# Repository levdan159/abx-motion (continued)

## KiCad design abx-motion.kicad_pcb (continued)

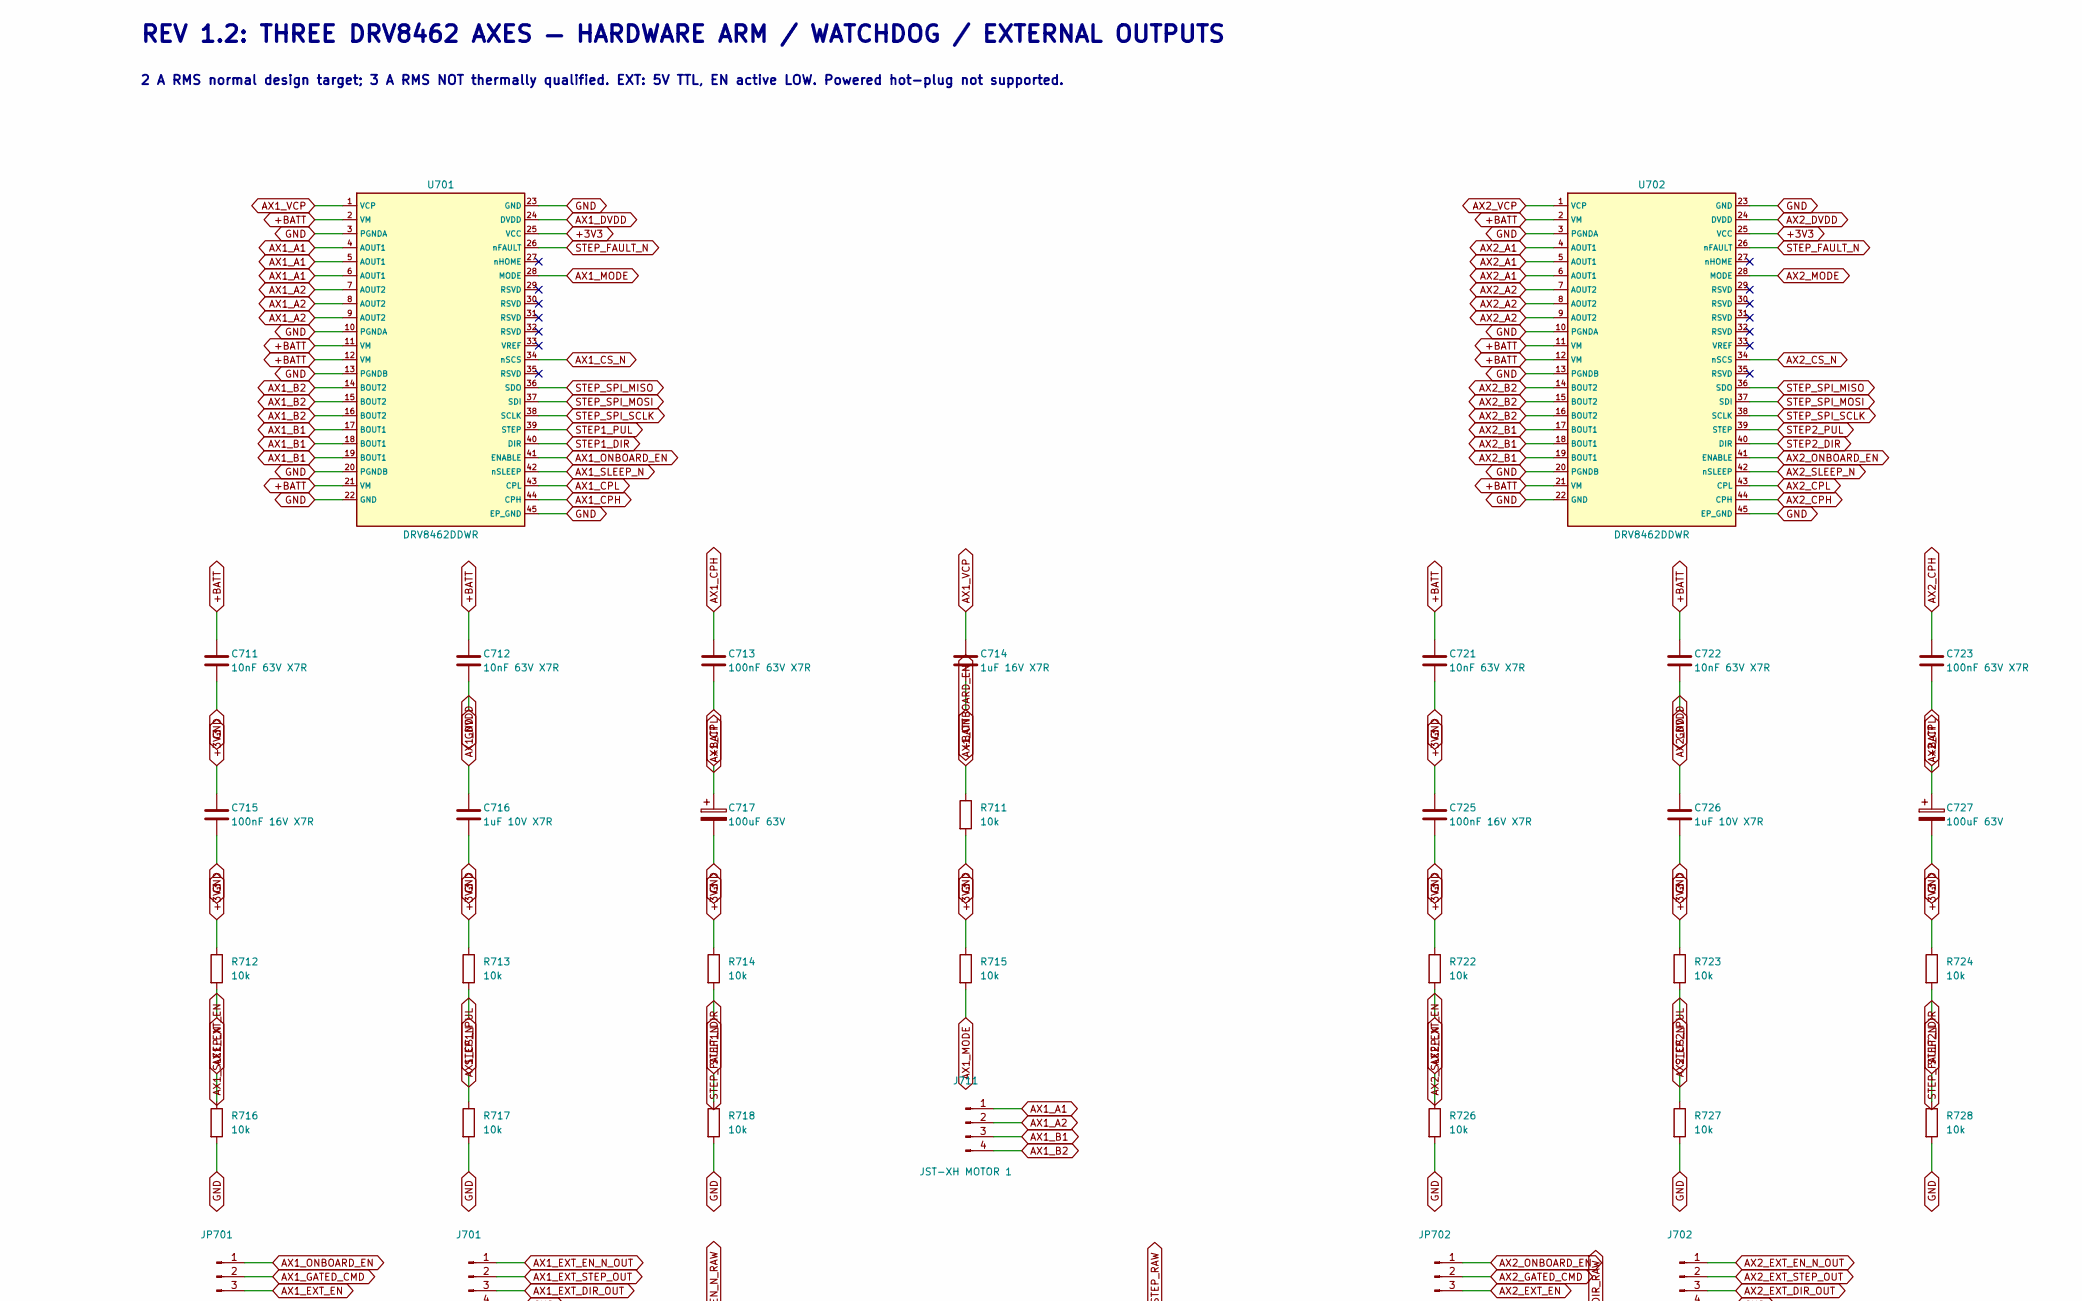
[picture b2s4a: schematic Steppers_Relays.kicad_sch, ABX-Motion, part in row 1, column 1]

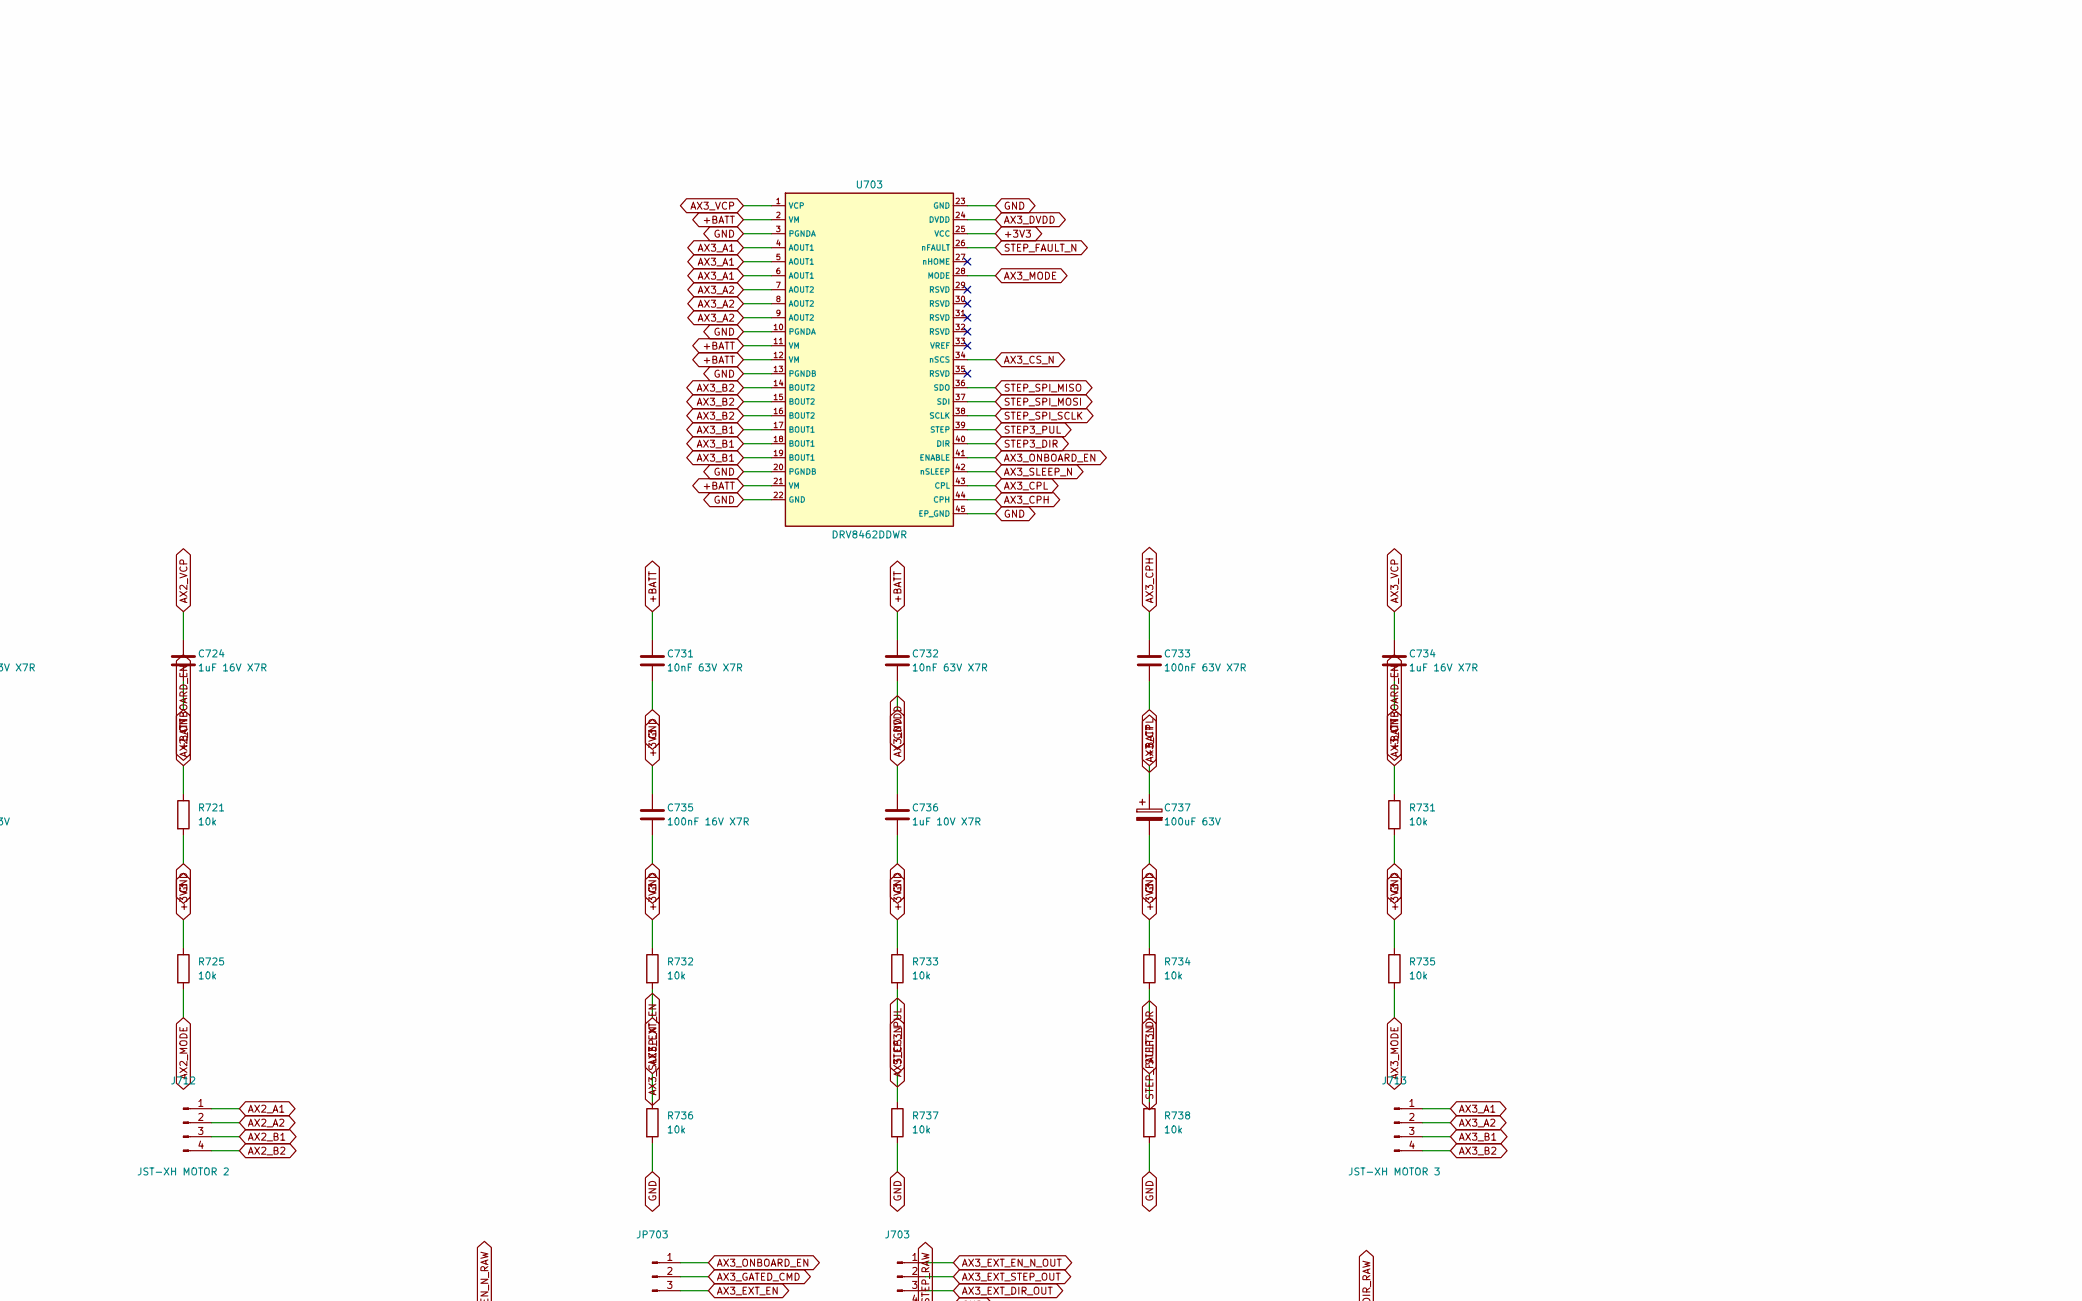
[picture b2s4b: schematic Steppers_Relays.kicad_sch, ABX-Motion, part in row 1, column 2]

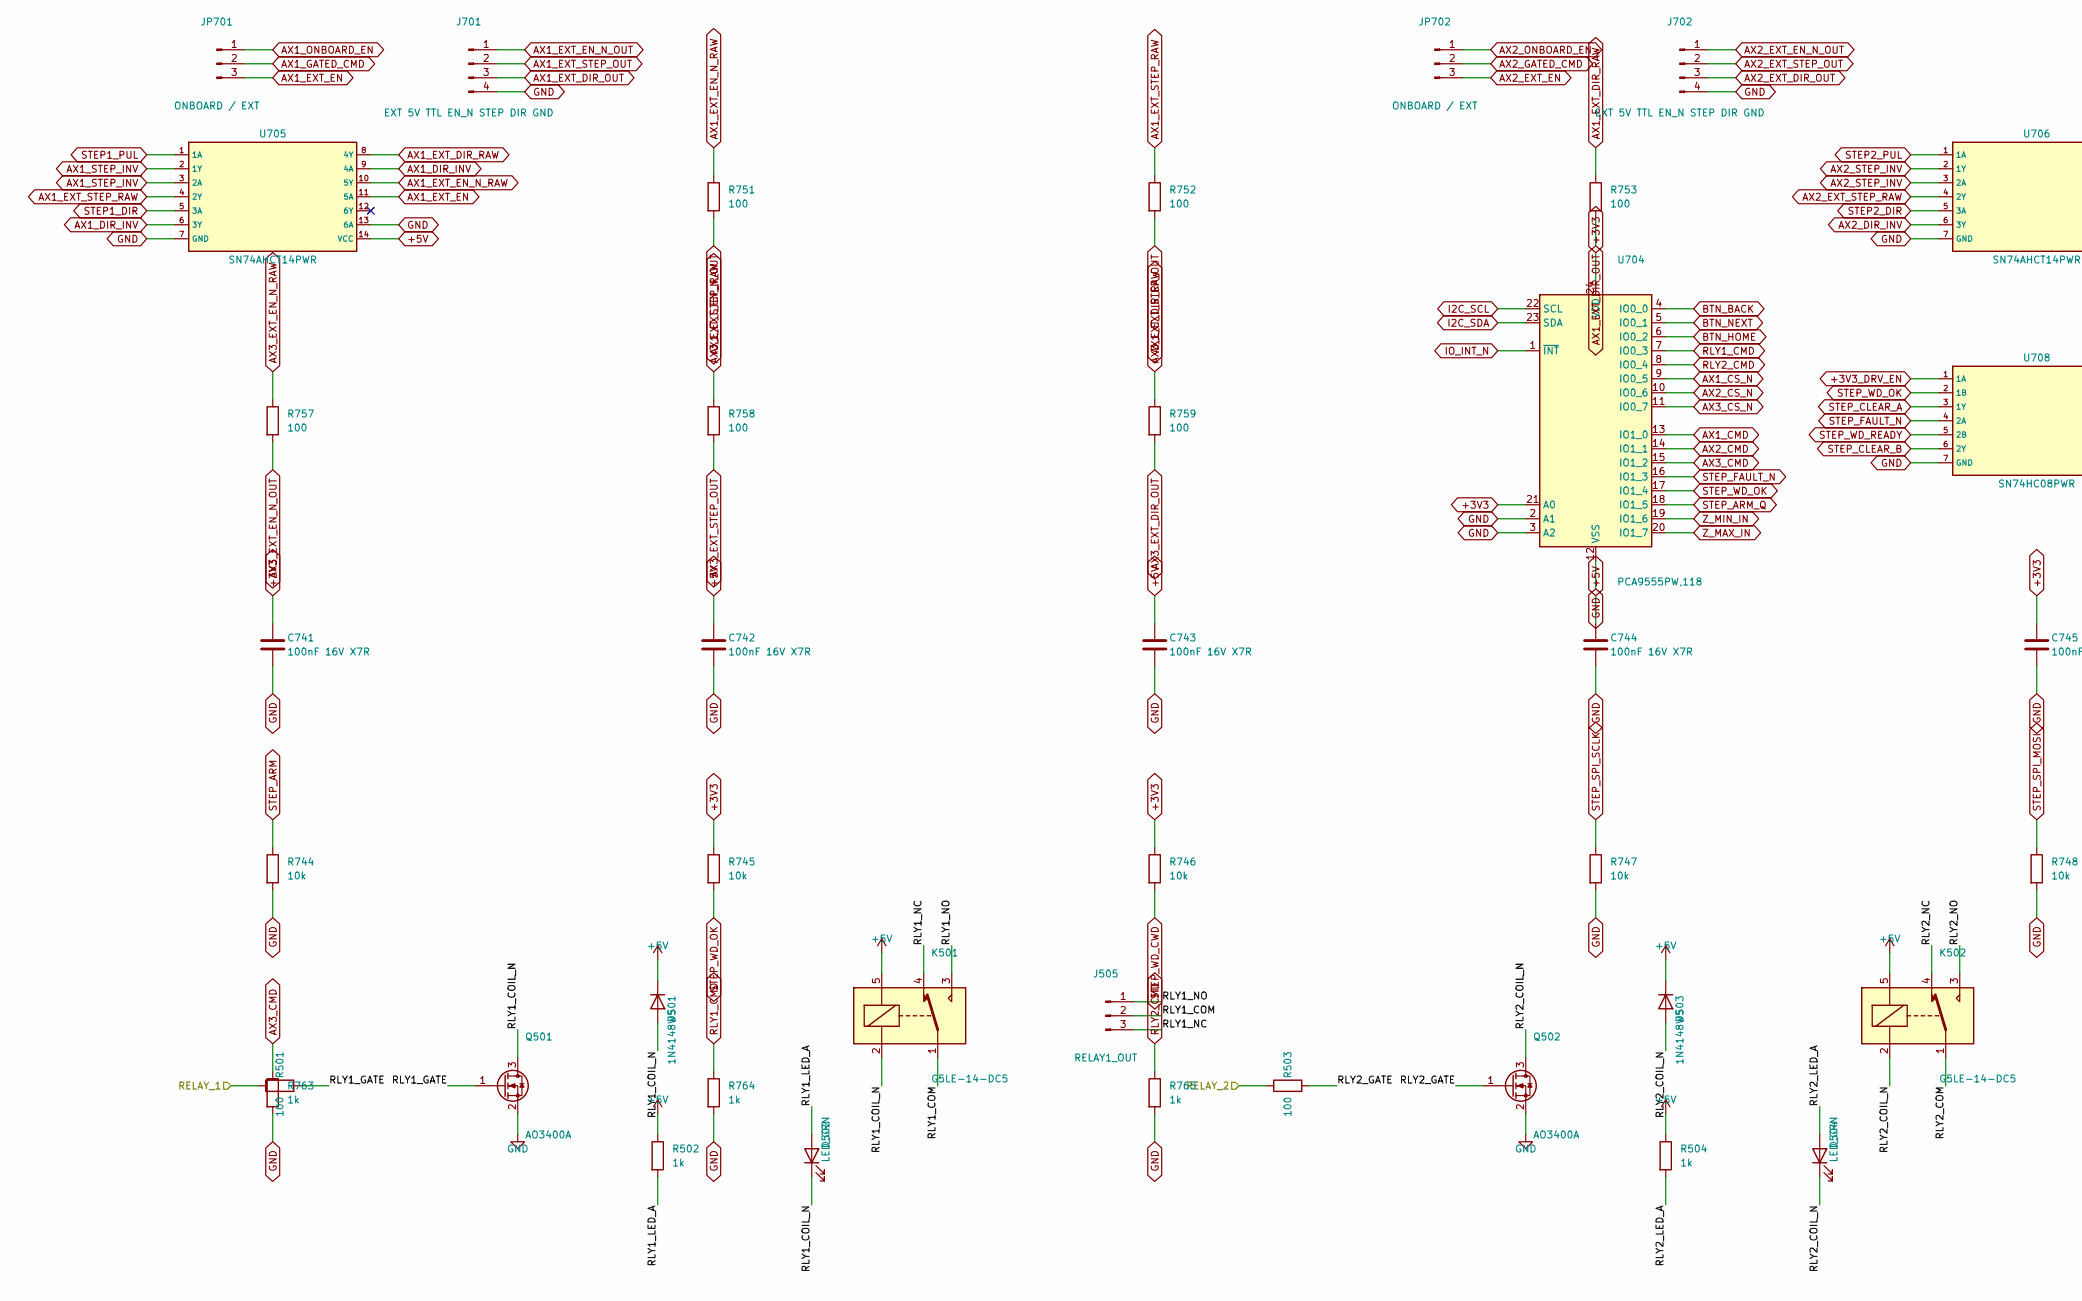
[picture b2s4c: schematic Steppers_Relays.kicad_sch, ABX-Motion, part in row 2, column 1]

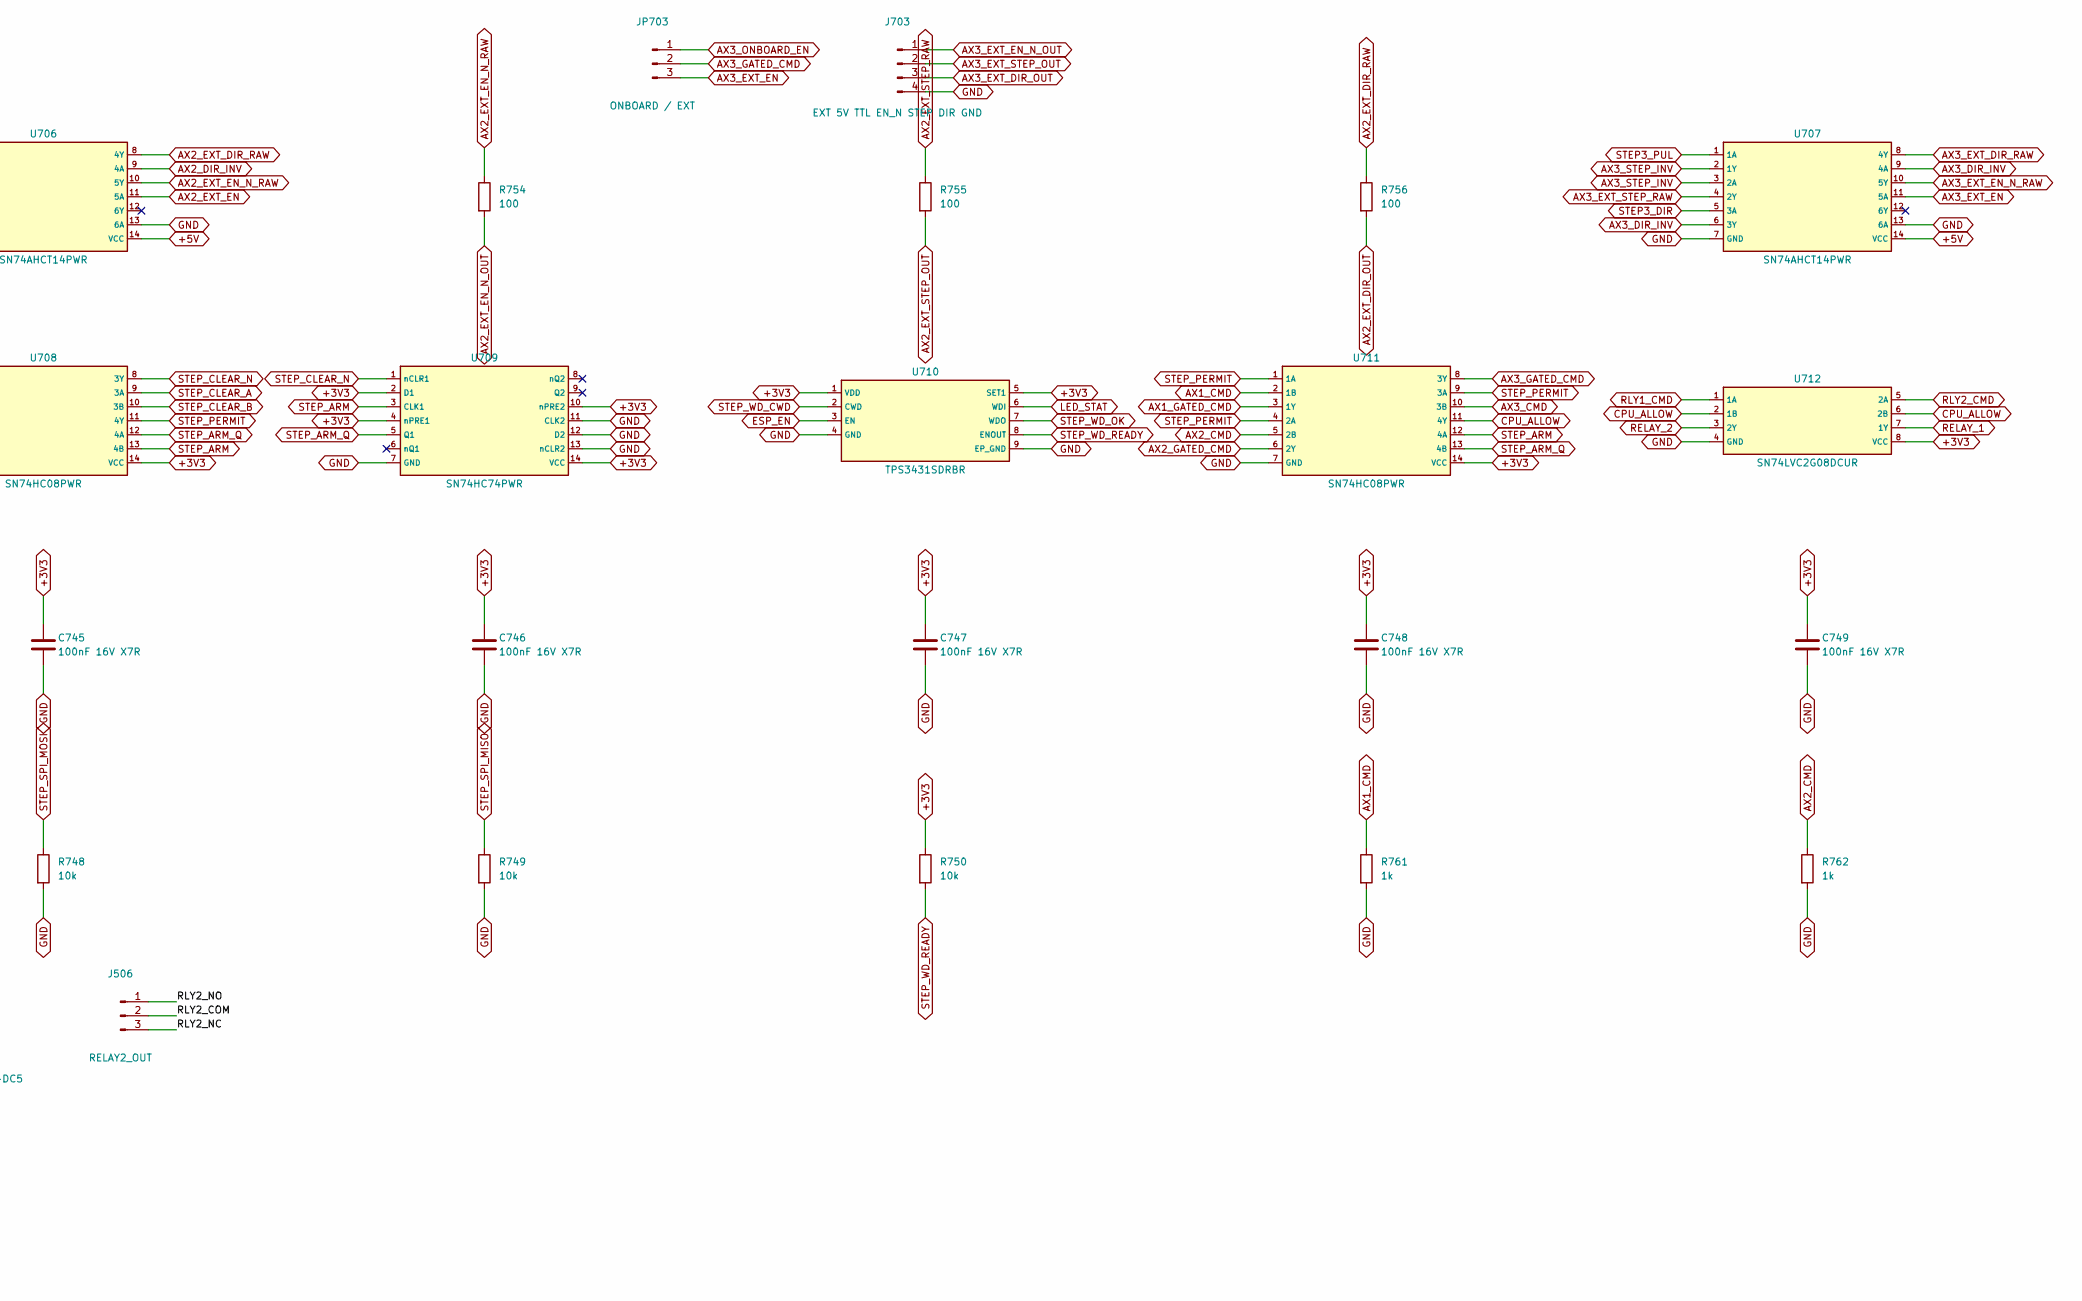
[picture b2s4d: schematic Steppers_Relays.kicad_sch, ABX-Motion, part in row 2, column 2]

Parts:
C711, C712, C721, C722, C731, C732: 10nF 63V X7R; C_0603_1608Metric; LCSC C162275
C713, C723, C733: 100nF 63V X7R; C_0603_1608Metric; LCSC C77058
C714, C724, C734: 1uF 16V X7R; C_0603_1608Metric; LCSC C59782
C715, C725, C735, C741, C742, C743, C744, C745, C746, C747, C748, C749: 100nF 16V X7R; C_0603_1608Metric; LCSC C14663
C716, C726, C736: 1uF 10V X7R; C_0603_1608Metric; LCSC C59782
C717, C727, C737: 100uF 63V; CP_Radial_D8.0mm_P3.50mm; LCSC C88747
D501, D503: 1N4148WS; D_SOD-323; LCSC C2128
D502, D504: LED_GRN; LED_0603_1608Metric; LCSC C12624
J505: RELAY1_OUT; ABX_J505_TerminalBlock_Phoenix_MKDS-1_5-3-5.08_1x03_P5.08mm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; LCSC C72334
J506: RELAY2_OUT; ABX_J506_TerminalBlock_Phoenix_MKDS-1_5-3-5.08_1x03_P5.08mm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; LCSC C72334
J701, J702, J703: EXT 5V TTL EN_N STEP DIR GND; PinHeader_1x04_P2.54mm_Vertical; LCSC C492403
J711: JST-XH MOTOR 1; JST_XH_B4B-XH-A_1x04_P2.50mm_Vertical; LCSC C566014
J712: JST-XH MOTOR 2; JST_XH_B4B-XH-A_1x04_P2.50mm_Vertical; LCSC C566014
J713: JST-XH MOTOR 3; JST_XH_B4B-XH-A_1x04_P2.50mm_Vertical; LCSC C566014
JP701, JP702, JP703: ONBOARD / EXT; PinHeader_1x03_P2.54mm_Vertical; LCSC C492402
K501, K502: G5LE-14-DC5; Relay_SPDT_Omron-G5LE-1; LCSC C116963
Q501, Q502: AO3400A; SOT-23; LCSC C20917
R501, R503, R751, R752, R753, R754, R755, R756, R757, R758, R759: 100; R_0603_1608Metric; LCSC C22775
R502, R504, R761, R762, R763, R764, R765: 1k; R_0603_1608Metric; LCSC C21190
R711, R712, R713, R714, R715, R716, R717, R718, R721, R722, R723, R724, R725, R726, R727, R728, R731, R732, R733, R734, R735, R736, R737, R738, R744, R745, R746, R747, R748, R749, R750: 10k; R_0603_1608Metric; LCSC C25804
U701, U702, U703: DRV8462DDWR; DRV8462_DDW0044E; LCSC C5930226
U704: PCA9555PW,118; TSSOP-24_4.4x7.8mm_P0.65mm; LCSC C128392
U705, U706, U707: SN74AHCT14PWR; TSSOP-14_4.4x5mm_P0.65mm; LCSC C7481
U708, U711: SN74HC08PWR; TSSOP-14_4.4x5mm_P0.65mm; LCSC C7642
U709: SN74HC74PWR; TSSOP-14_4.4x5mm_P0.65mm; LCSC C6761
U710: TPS3431SDRBR; TPS3431_DRB0008A; LCSC C702145
U712: SN74LVC2G08DCUR; VSSOP-8_2.3x2mm_P0.5mm; LCSC C91875

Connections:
+3V3: C715.1, C725.1, C735.1, C741.1, C745.1, C746.1, C747.1, C748.1, C749.1, R712.1, R713.1, R714.1, R715.1, R722.1, R723.1, R724.1, R725.1, R732.1, R733.1, R734.1, R735.1, R745.1, R746.1, R750.1, U701.25 (VCC), U702.25 (VCC), U703.25 (VCC), U704.21 (A0), U704.24 (VDD), U708.14 (VCC), U709.2 (D1), U709.4 (nPRE1), U709.10 (nPRE2), U709.14 (VCC), U710.1 (VDD), U710.5 (SET1), U711.14 (VCC), U712.8 (VCC); also elsewhere on the board
+3V3_DRV_EN: U708.1 (1A); also elsewhere on the board
+5V: C742.1, C743.1, C744.1, D501.1 (K), D503.1 (K), K501.5, K502.5, R502.1, R504.1, U705.14 (VCC), U706.14 (VCC), U707.14 (VCC); also elsewhere on the board
/Steppers_and_Relays/RLY1_COIL_N: D501.2 (A), D502.1 (K), K501.2, Q501.3 (D)
/Steppers_and_Relays/RLY1_COM: J505.2, K501.1
/Steppers_and_Relays/RLY1_GATE: Q501.1 (G), R501.2
/Steppers_and_Relays/RLY1_LED_A: D502.2 (A), R502.2
/Steppers_and_Relays/RLY1_NC: J505.3, K501.4
/Steppers_and_Relays/RLY1_NO: J505.1, K501.3
/Steppers_and_Relays/RLY2_COIL_N: D503.2 (A), D504.1 (K), K502.2, Q502.3 (D)
/Steppers_and_Relays/RLY2_COM: J506.2, K502.1
/Steppers_and_Relays/RLY2_GATE: Q502.1 (G), R503.2
/Steppers_and_Relays/RLY2_LED_A: D504.2 (A), R504.2
/Steppers_and_Relays/RLY2_NC: J506.3, K502.4
/Steppers_and_Relays/RLY2_NO: J506.1, K502.3
AX1_A1: J711.1, U701.4 (AOUT1), U701.5 (AOUT1), U701.6 (AOUT1)
AX1_A2: J711.2, U701.7 (AOUT2), U701.8 (AOUT2), U701.9 (AOUT2)
AX1_B1: J711.3, U701.17 (BOUT1), U701.18 (BOUT1), U701.19 (BOUT1)
AX1_B2: J711.4, U701.14 (BOUT2), U701.15 (BOUT2), U701.16 (BOUT2)
AX1_CMD: R761.1, U704.13 (IO1_0), U711.2 (1B)
AX1_CPH: C713.1, U701.44 (CPH)
AX1_CPL: C713.2, U701.43 (CPL)
AX1_CS_N: R713.2, U701.34 (nSCS), U704.9 (IO0_5)
AX1_DIR_INV: U705.6 (3Y), U705.9 (4A)
AX1_DVDD: C716.1, U701.24 (DVDD)
AX1_EXT_DIR_OUT: J701.3, R753.2
AX1_EXT_DIR_RAW: R753.1, U705.8 (4Y)
AX1_EXT_EN: JP701.3, R716.1, U705.11 (5A)
AX1_EXT_EN_N_OUT: J701.1, R751.2
AX1_EXT_EN_N_RAW: R751.1, U705.10 (5Y)
AX1_EXT_STEP_OUT: J701.2, R752.2
AX1_EXT_STEP_RAW: R752.1, U705.4 (2Y)
AX1_GATED_CMD: JP701.2, U711.3 (1Y)
AX1_MODE: R715.2, U701.28 (MODE)
AX1_ONBOARD_EN: JP701.1, R711.1, U701.41 (ENABLE)
AX1_SLEEP_N: R712.2, U701.42 (nSLEEP)
AX1_STEP_INV: U705.2 (1Y), U705.3 (2A)
AX1_VCP: C714.1, U701.1 (VCP)
AX2_A1: J712.1, U702.4 (AOUT1), U702.5 (AOUT1), U702.6 (AOUT1)
AX2_A2: J712.2, U702.7 (AOUT2), U702.8 (AOUT2), U702.9 (AOUT2)
AX2_B1: J712.3, U702.17 (BOUT1), U702.18 (BOUT1), U702.19 (BOUT1)
AX2_B2: J712.4, U702.14 (BOUT2), U702.15 (BOUT2), U702.16 (BOUT2)
AX2_CMD: R762.1, U704.14 (IO1_1), U711.5 (2B)
AX2_CPH: C723.1, U702.44 (CPH)
AX2_CPL: C723.2, U702.43 (CPL)
AX2_CS_N: R723.2, U702.34 (nSCS), U704.10 (IO0_6)
AX2_DIR_INV: U706.6 (3Y), U706.9 (4A)
AX2_DVDD: C726.1, U702.24 (DVDD)
AX2_EXT_DIR_OUT: J702.3, R756.2
AX2_EXT_DIR_RAW: R756.1, U706.8 (4Y)
AX2_EXT_EN: JP702.3, R726.1, U706.11 (5A)
AX2_EXT_EN_N_OUT: J702.1, R754.2
AX2_EXT_EN_N_RAW: R754.1, U706.10 (5Y)
AX2_EXT_STEP_OUT: J702.2, R755.2
AX2_EXT_STEP_RAW: R755.1, U706.4 (2Y)
AX2_GATED_CMD: JP702.2, U711.6 (2Y)
AX2_MODE: R725.2, U702.28 (MODE)
AX2_ONBOARD_EN: JP702.1, R721.1, U702.41 (ENABLE)
AX2_SLEEP_N: R722.2, U702.42 (nSLEEP)
AX2_STEP_INV: U706.2 (1Y), U706.3 (2A)
AX2_VCP: C724.1, U702.1 (VCP)
AX3_A1: J713.1, U703.4 (AOUT1), U703.5 (AOUT1), U703.6 (AOUT1)
AX3_A2: J713.2, U703.7 (AOUT2), U703.8 (AOUT2), U703.9 (AOUT2)
AX3_B1: J713.3, U703.17 (BOUT1), U703.18 (BOUT1), U703.19 (BOUT1)
AX3_B2: J713.4, U703.14 (BOUT2), U703.15 (BOUT2), U703.16 (BOUT2)
AX3_CMD: R763.1, U704.15 (IO1_2), U711.10 (3B)
AX3_CPH: C733.1, U703.44 (CPH)
AX3_CPL: C733.2, U703.43 (CPL)
AX3_CS_N: R733.2, U703.34 (nSCS), U704.11 (IO0_7)
AX3_DIR_INV: U707.6 (3Y), U707.9 (4A)
AX3_DVDD: C736.1, U703.24 (DVDD)
AX3_EXT_DIR_OUT: J703.3, R759.2
AX3_EXT_DIR_RAW: R759.1, U707.8 (4Y)
AX3_EXT_EN: JP703.3, R736.1, U707.11 (5A)
AX3_EXT_EN_N_OUT: J703.1, R757.2
AX3_EXT_EN_N_RAW: R757.1, U707.10 (5Y)
AX3_EXT_STEP_OUT: J703.2, R758.2
AX3_EXT_STEP_RAW: R758.1, U707.4 (2Y)
AX3_GATED_CMD: JP703.2, U711.8 (3Y)
AX3_MODE: R735.2, U703.28 (MODE)
AX3_ONBOARD_EN: JP703.1, R731.1, U703.41 (ENABLE)
AX3_SLEEP_N: R732.2, U703.42 (nSLEEP)
AX3_STEP_INV: U707.2 (1Y), U707.3 (2A)
AX3_VCP: C734.1, U703.1 (VCP)
BTN_BACK: U704.4 (IO0_0); also elsewhere on the board
BTN_HOME: U704.6 (IO0_2); also elsewhere on the board
BTN_NEXT: U704.5 (IO0_1); also elsewhere on the board
CPU_ALLOW: U711.11 (4Y), U712.2 (1B), U712.6 (2B)
ESP_EN: U710.3 (EN); also elsewhere on the board
I2C_SCL: U704.22 (SCL); also elsewhere on the board
I2C_SDA: U704.23 (SDA); also elsewhere on the board
IO_INT_N: U704.1 (~INT); also elsewhere on the board
LED_STAT: U710.6 (WDI); also elsewhere on the board
RELAY_1: R501.1, U712.7 (1Y); also elsewhere on the board
RELAY_2: R503.1, U712.3 (2Y); also elsewhere on the board
RLY1_CMD: R764.1, U704.7 (IO0_3), U712.1 (1A)
RLY2_CMD: R765.1, U704.8 (IO0_4), U712.5 (2A)
STEP1_DIR: R718.1, U701.40 (DIR), U705.5 (3A); also elsewhere on the board
STEP1_PUL: R717.1, U701.39 (STEP), U705.1 (1A); also elsewhere on the board
STEP2_DIR: R728.1, U702.40 (DIR), U706.5 (3A); also elsewhere on the board
STEP2_PUL: R727.1, U702.39 (STEP), U706.1 (1A); also elsewhere on the board
STEP3_DIR: R738.1, U703.40 (DIR), U707.5 (3A); also elsewhere on the board
STEP3_PUL: R737.1, U703.39 (STEP), U707.1 (1A); also elsewhere on the board
STEP_ARM: R744.1, U708.13 (4B), U709.3 (CLK1), U711.12 (4A); also elsewhere on the board
STEP_ARM_Q: U704.18 (IO1_5), U708.12 (4A), U709.5 (Q1), U711.13 (4B)
STEP_CLEAR_A: U708.3 (1Y), U708.9 (3A)
STEP_CLEAR_B: U708.6 (2Y), U708.10 (3B)
STEP_CLEAR_N: U708.8 (3Y), U709.1 (nCLR1)
STEP_FAULT_N: R714.2, R724.2, R734.2, U701.26 (nFAULT), U702.26 (nFAULT), U703.26 (nFAULT), U704.16 (IO1_3), U708.4 (2A)
STEP_PERMIT: U708.11 (4Y), U711.1 (1A), U711.4 (2A), U711.9 (3A)
STEP_SPI_MISO: R749.1, U701.36 (SDO), U702.36 (SDO), U703.36 (SDO); also elsewhere on the board
STEP_SPI_MOSI: R748.1, U701.37 (SDI), U702.37 (SDI), U703.37 (SDI); also elsewhere on the board
STEP_SPI_SCLK: R747.1, U701.38 (SCLK), U702.38 (SCLK), U703.38 (SCLK); also elsewhere on the board
STEP_WD_CWD: R746.2, U710.2 (CWD)
STEP_WD_OK: R745.2, U704.17 (IO1_4), U708.2 (1B), U710.7 (WDO)
STEP_WD_READY: R750.2, U708.5 (2B), U710.8 (ENOUT)
Z_MAX_IN: U704.20 (IO1_7); also elsewhere on the board
Z_MIN_IN: U704.19 (IO1_6); also elsewhere on the board

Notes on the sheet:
REV 1.2: THREE DRV8462 AXES — HARDWARE ARM / WATCHDOG / EXTERNAL OUTPUTS
2 A RMS normal design target; 3 A RMS NOT thermally qualified. EXT: 5V TTL, EN active LOW. Powered hot-plug not supported.

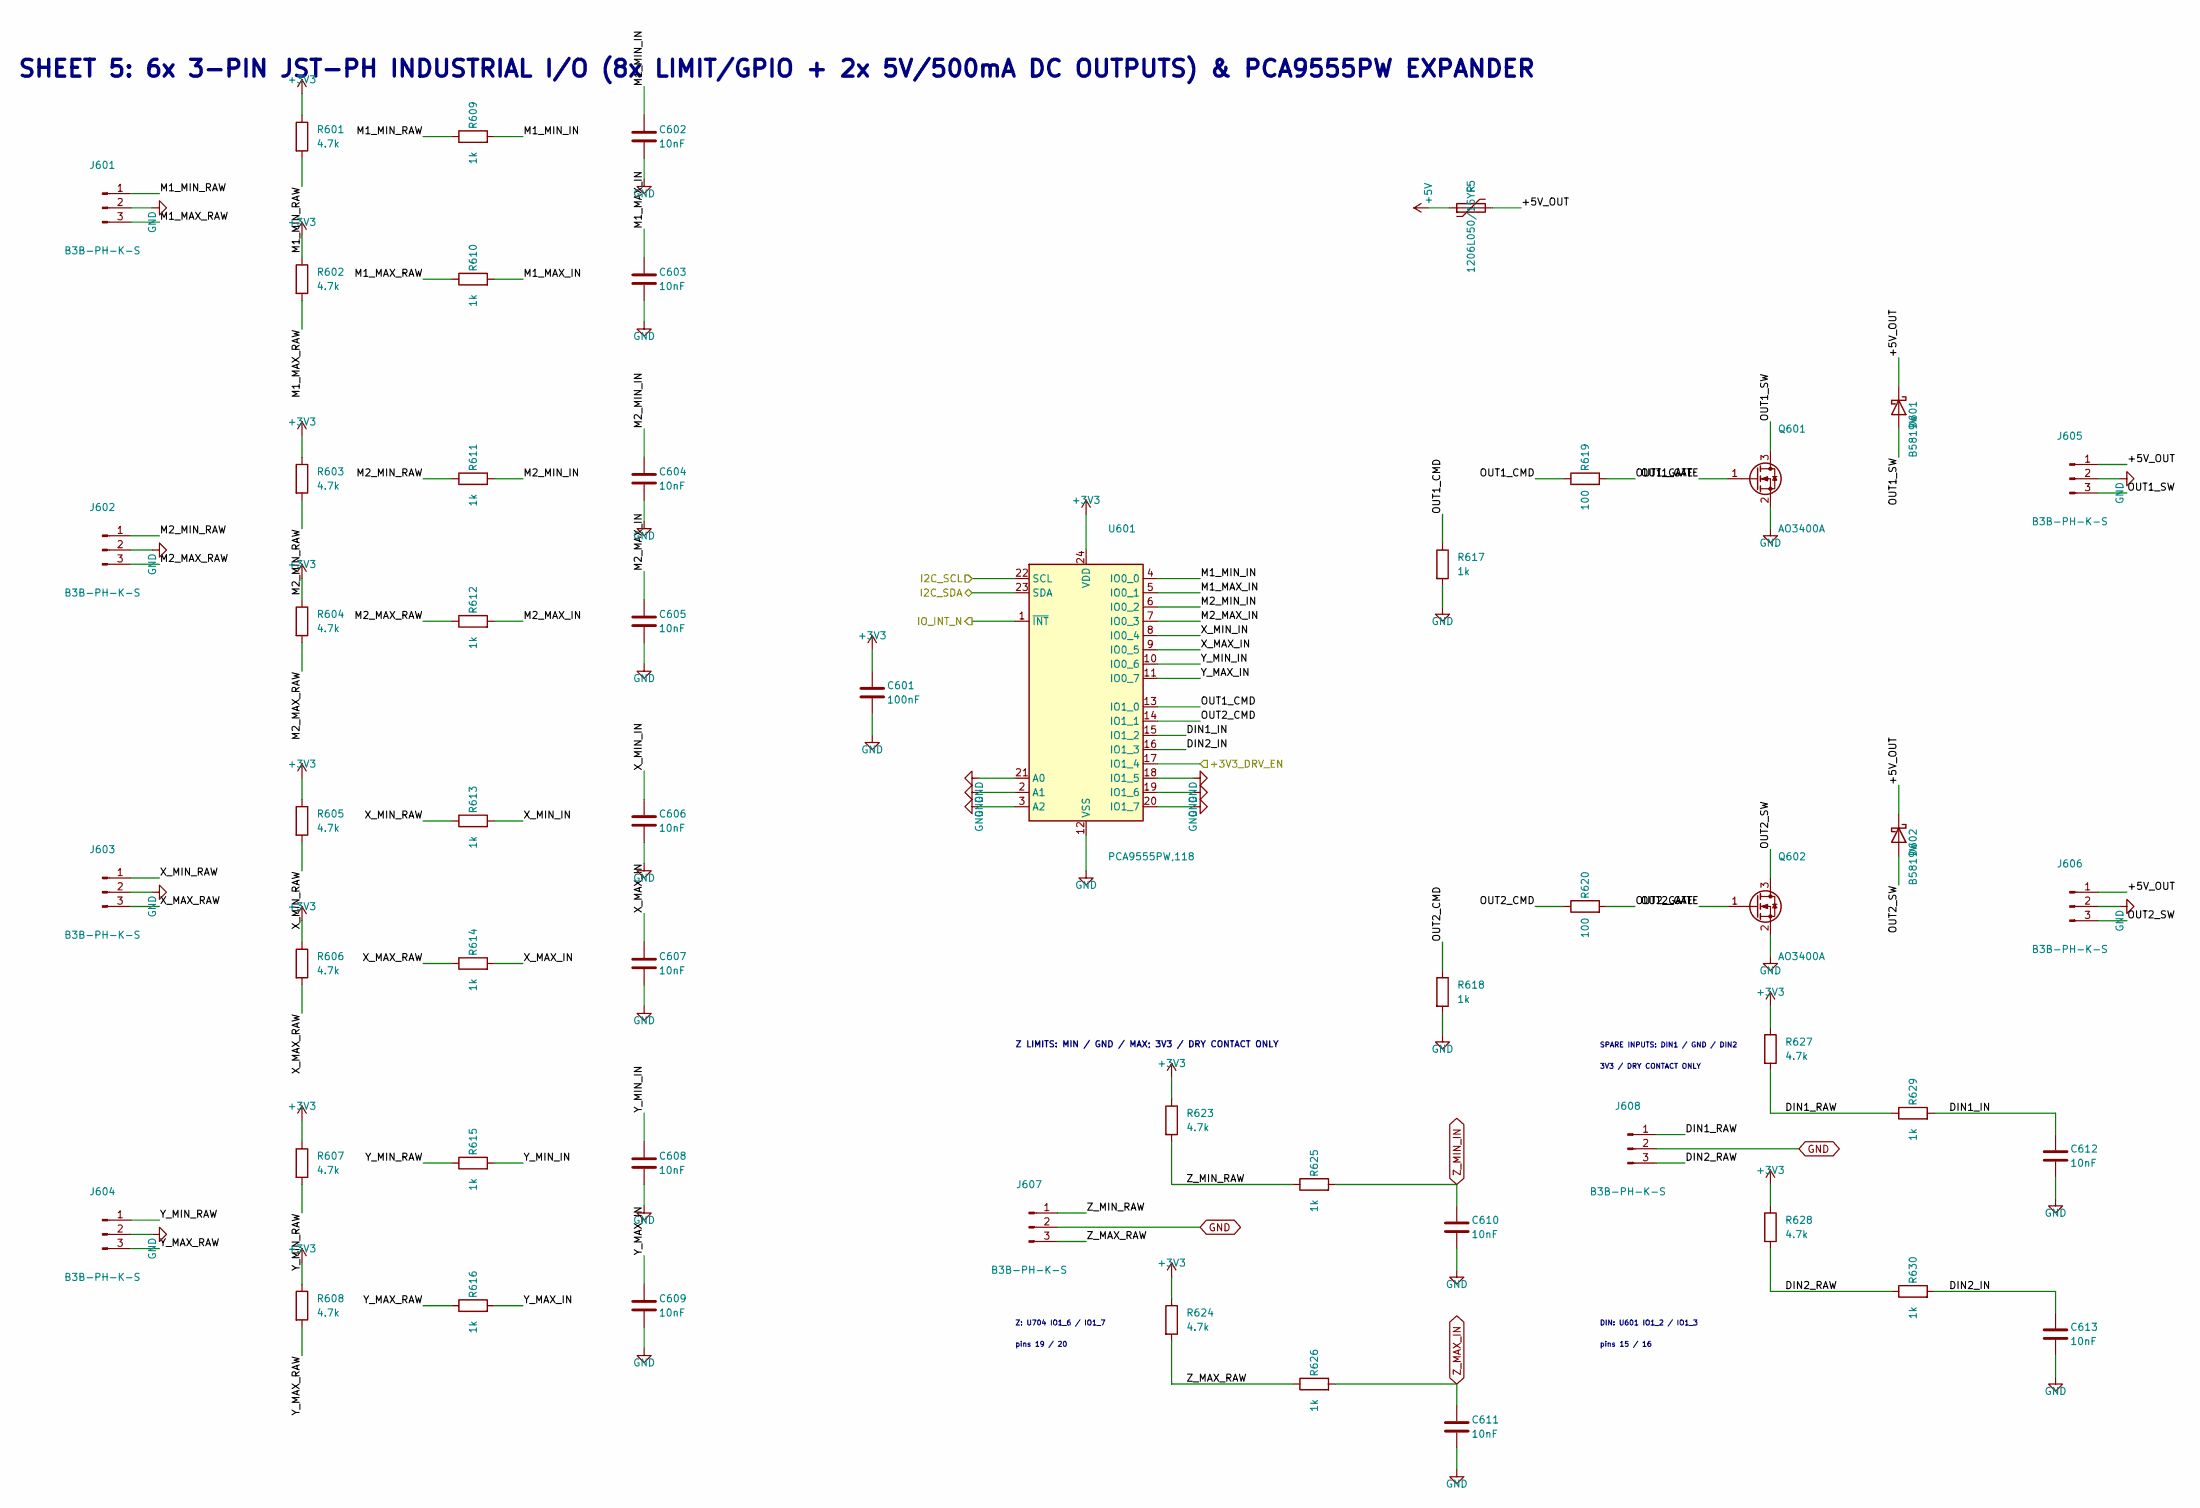
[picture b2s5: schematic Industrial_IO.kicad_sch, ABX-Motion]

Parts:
C601: 100nF; C_0603_1608Metric; LCSC C14663
C602, C603, C604, C605, C606, C607, C608, C609, C610, C611, C612, C613: 10nF; C_0603_1608Metric; LCSC C57112
D601, D602: B5819W; D_SOD-123; LCSC C8598
F5: 1206L050/15YR; Fuse_1206_3216Metric; LCSC C151162
J601, J602, J603, J604, J605, J606, J607, J608: B3B-PH-K-S; JST_PH_B3B-PH-K_1x03_P2.00mm_Vertical; LCSC C131339
Q601, Q602: AO3400A; SOT-23; LCSC C20917
R601, R602, R603, R604, R605, R606, R607, R608, R623, R624, R627, R628: 4.7k; R_0603_1608Metric; LCSC C23162
R609, R610, R611, R612, R613, R614, R615, R616, R617, R618, R625, R626, R629, R630: 1k; R_0603_1608Metric; LCSC C21190
R619, R620: 100; R_0603_1608Metric; LCSC C22775
U601: PCA9555PW,118; TSSOP-24_4.4x7.8mm_P0.65mm; LCSC C128392

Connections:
+3V3: C601.1, R601.1, R602.1, R603.1, R604.1, R605.1, R606.1, R607.1, R608.1, R623.1, R624.1, R627.1, R628.1, U601.24 (VDD); also elsewhere on the board
+3V3_DRV_EN: U601.17 (IO1_4); also elsewhere on the board
+5V: F5.1; also elsewhere on the board
/Industrial_IO/+5V_OUT: D601.1 (K), D602.1 (K), F5.2, J605.1, J606.1
/Industrial_IO/DIN1_IN: C612.1, R629.2, U601.15 (IO1_2)
/Industrial_IO/DIN1_RAW: J608.1, R627.2, R629.1
/Industrial_IO/DIN2_IN: C613.1, R630.2, U601.16 (IO1_3)
/Industrial_IO/DIN2_RAW: J608.3, R628.2, R630.1
/Industrial_IO/M1_MAX_IN: C603.1, R610.2, U601.5 (IO0_1)
/Industrial_IO/M1_MAX_RAW: J601.3, R602.2, R610.1
/Industrial_IO/M1_MIN_IN: C602.1, R609.2, U601.4 (IO0_0)
/Industrial_IO/M1_MIN_RAW: J601.1, R601.2, R609.1
/Industrial_IO/M2_MAX_IN: C605.1, R612.2, U601.7 (IO0_3)
/Industrial_IO/M2_MAX_RAW: J602.3, R604.2, R612.1
/Industrial_IO/M2_MIN_IN: C604.1, R611.2, U601.6 (IO0_2)
/Industrial_IO/M2_MIN_RAW: J602.1, R603.2, R611.1
/Industrial_IO/OUT1_CMD: R617.1, R619.1, U601.13 (IO1_0)
/Industrial_IO/OUT1_GATE: Q601.1 (G), R619.2
/Industrial_IO/OUT1_SW: D601.2 (A), J605.3, Q601.3 (D)
/Industrial_IO/OUT2_CMD: R618.1, R620.1, U601.14 (IO1_1)
/Industrial_IO/OUT2_GATE: Q602.1 (G), R620.2
/Industrial_IO/OUT2_SW: D602.2 (A), J606.3, Q602.3 (D)
/Industrial_IO/X_MAX_IN: C607.1, R614.2, U601.9 (IO0_5)
/Industrial_IO/X_MAX_RAW: J603.3, R606.2, R614.1
/Industrial_IO/X_MIN_IN: C606.1, R613.2, U601.8 (IO0_4)
/Industrial_IO/X_MIN_RAW: J603.1, R605.2, R613.1
/Industrial_IO/Y_MAX_IN: C609.1, R616.2, U601.11 (IO0_7)
/Industrial_IO/Y_MAX_RAW: J604.3, R608.2, R616.1
/Industrial_IO/Y_MIN_IN: C608.1, R615.2, U601.10 (IO0_6)
/Industrial_IO/Y_MIN_RAW: J604.1, R607.2, R615.1
/Industrial_IO/Z_MAX_RAW: J607.3, R624.2, R626.1
/Industrial_IO/Z_MIN_RAW: J607.1, R623.2, R625.1
I2C_SCL: U601.22 (SCL); also elsewhere on the board
I2C_SDA: U601.23 (SDA); also elsewhere on the board
IO_INT_N: U601.1 (~INT); also elsewhere on the board
Z_MAX_IN: C611.1, R626.2; also elsewhere on the board
Z_MIN_IN: C610.1, R625.2; also elsewhere on the board

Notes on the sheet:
SHEET 5: 6x 3-PIN JST-PH INDUSTRIAL I/O (8x LIMIT/GPIO + 2x 5V/500mA DC OUTPUTS) & PCA9555PW EXPANDER
Z LIMITS: MIN / GND / MAX; 3V3 / DRY CONTACT ONLY
SPARE INPUTS: DIN1 / GND / DIN2
3V3 / DRY CONTACT ONLY
Z: U704 IO1_6 / IO1_7
pins 19 / 20
DIN: U601 IO1_2 / IO1_3
pins 15 / 16
